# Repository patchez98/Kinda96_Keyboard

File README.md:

# Kinda96_Keyboard
Kinda a 96% keyboard, except the numpad is removable (and located on the left side) and there's a split spacebar. Also, it's wired/wireless thanks to the TinyPico Nano.

There are three KiCAD projects here, each with a different keyboard.

Full_96 holds a project with a single-board 96% keyboard. This is the simplest and cheapest option.

Full_75 holds a project with a 75% keyboard PCB. This board has a connector on the left side that can supply power to the numpad.

Numpad holds a project with a standalone wired/wireless numpad, with the option for power delivery from the 75% board.

I made the project like this for a number of reasons, the most notable being my ability to 3D print an entire case/plate in one go on my Artillery Sidewinder X1. Other than that, options are nice, I guess. Regardless, the full 96% board exists in case I get access to a larger printer sometime in the future.

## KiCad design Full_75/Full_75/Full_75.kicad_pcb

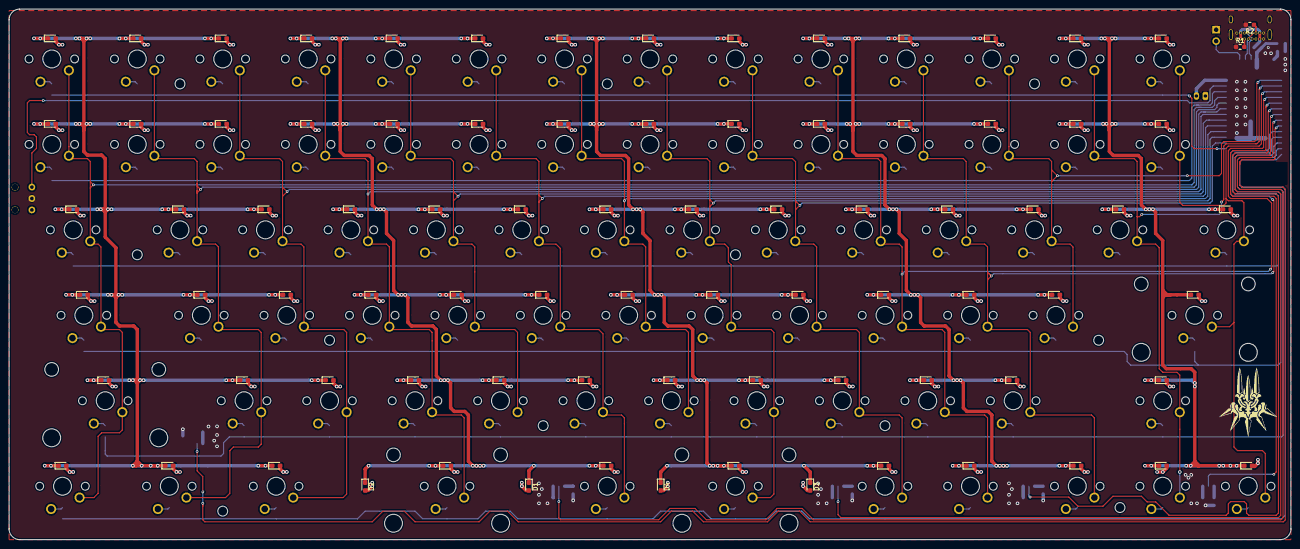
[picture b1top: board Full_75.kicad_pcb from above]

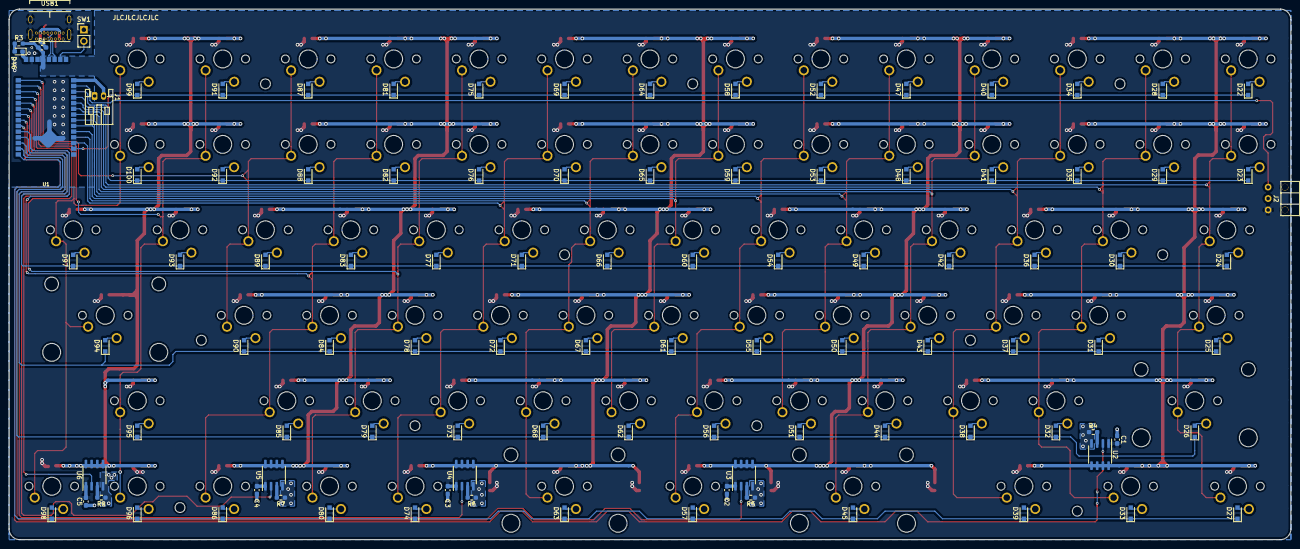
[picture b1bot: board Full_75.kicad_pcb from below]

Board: 2 copper layers, 285.7 x 118.3 mm, 185 parts (101 on the bottom side), 125 nets.

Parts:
C1, C2, C3, C4, C5: 2.2u; C_0603_1608Metric_Pad1.08x0.95mm_HandSolder
D1, D2, D3, D4: LED; LED_0603_1608Metric_Pad1.05x0.95mm_HandSolder
D22, D23, D24, D25, D26, D27, D28, D29, D30, D31, D32, D33, D34, D35, D36, D37, D38, D39, D40, D41, D42, D43, D44, D45, D47, D48, D49, D50, D51, D52, D53, D54, D55, D56, D57, D58, D59, D60, D61, D62, D63, D64, D65, D66, D67, D68, D69, D70, D71, D72, D73, D74, D75, D76, D77, D78, D79, D80, D81, D82, D83, D84, D85, D86, D87, D88, D89, D90, D91, D92, D93, D94, D95, D96, D97, D98, D99, D100: D; D_SOD-323_HandSoldering
D46: BATT_LED; LED_0603_1608Metric_Pad1.05x0.95mm_HandSolder
F1: 500mA; Fuse_0603_1608Metric_Pad1.05x0.95mm_HandSolder
J1: Battery; JST_PH_S2B-PH-K_1x02_P2.00mm_Horizontal
J2: Numpad_PWR; 01x03_MillMax_Springloaded_Pin
MX22: ESC; MXOnly-1U
MX23: `; MXOnly-1U
MX24: Tab; MXOnly-1.5U
MX25: Caps; MXOnly-1.75U
MX26: Shift; MXOnly-2.25U
MX27: LCtrl; MXOnly-1.25U
MX28: F1; MXOnly-1U
MX29: 1; MXOnly-1U
MX30: Q; MXOnly-1U
MX31: A; MXOnly-1U
MX32: Z; MXOnly-1U
MX33: Win; MXOnly-1.25U
MX34: F2; MXOnly-1U
MX35: 2; MXOnly-1U
MX36: W; MXOnly-1U
MX37: S; MXOnly-1U
MX38: X; MXOnly-1U
MX39: LAlt; MXOnly-1.25U
MX40: F3; MXOnly-1U
MX41: 3; MXOnly-1U
MX42: E; MXOnly-1U
MX43: D; MXOnly-1U
MX44: C; MXOnly-1U
MX45: Space; MXOnly-2.75U
MX46: F4; MXOnly-1U
MX47: 4; MXOnly-1U
MX48: R; MXOnly-1U
MX49: F; MXOnly-1U
MX50: V; MXOnly-1U
MX51: F5; MXOnly-1U
MX52: 5; MXOnly-1U
MX53: T; MXOnly-1U
MX54: G; MXOnly-1U
MX55: B; MXOnly-1U
MX56: Del; MXOnly-1U
MX57: F6; MXOnly-1U
MX58: 6; MXOnly-1U
MX59: Y; MXOnly-1U
MX60: H; MXOnly-1U
MX61: N; MXOnly-1U
MX62: Backspace; MXOnly-2U
MX63: F7; MXOnly-1U
MX64: 7; MXOnly-1U
MX65: U; MXOnly-1U
MX66: J; MXOnly-1U
MX67: M; MXOnly-1U
MX68: F8; MXOnly-1U
MX69: 8; MXOnly-1U
MX70: I; MXOnly-1U
MX71: K; MXOnly-1U
MX72: ,; MXOnly-1U
MX73: Home; MXOnly-1U
MX74: F9; MXOnly-1U
MX75: 9; MXOnly-1U
MX76: O; MXOnly-1U
MX77: L; MXOnly-1U
MX78: .; MXOnly-1U
MX79: End; MXOnly-1U
MX80: F10; MXOnly-1U
MX81: 0; MXOnly-1U
MX82: P; MXOnly-1U
MX83: ;; MXOnly-1U
MX84: /; MXOnly-1U
MX85: Left; MXOnly-1U
MX86: F11; MXOnly-1U
MX87: -; MXOnly-1U
MX88: [; MXOnly-1U
MX89: '; MXOnly-1U
MX90: F12; MXOnly-1U
MX91: =; MXOnly-1U
MX92: ]; MXOnly-1U
MX93: Enter; MXOnly-2.25U
MX94: Up; MXOnly-1U
MX95: Down; MXOnly-1U
MX96: \; MXOnly-1.5U
MX97: Right; MXOnly-1U
MX98: PgUp; MXOnly-1U
MX99: PgDn; MXOnly-1U
R1, R2: 5.1k; R_0603_1608Metric_Pad0.98x0.95mm_HandSolder
R3: 2k; R_0603_1608Metric_Pad0.98x0.95mm_HandSolder
R4, R5, R6, R7, R8: 16k; R_0603_1608Metric_Pad0.98x0.95mm_HandSolder
SW1: SW_DIP_x01; PinHeader_1x02_P2.54mm_Vertical
U1: TinyPICO_Nano
U2, U3, U4, U5, U6: MIC4801; SOIC-8_3.9x4.9mm_P1.27mm
USB1: USB4085-GF-A; USB_C_GCT_USB4085

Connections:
+5V: C1.2, C2.2, C3.2, C4.2, C5.2, D1.2, D2.2, D3.2, D4.2, F1.1, J2.1, MX22.3, MX23.3, MX24.3, MX25.3, MX26.3, MX27.3, MX28.3, MX29.3, MX30.3, MX31.3, MX32.3, MX33.3, MX34.3, MX35.3, MX36.3, MX37.3, MX38.3, MX39.3, MX40.3, MX41.3, MX42.3, MX43.3, MX44.3, MX45.3, MX46.3, MX47.3, MX48.3, MX49.3, MX50.3, MX51.3, MX52.3, MX53.3, MX54.3, MX55.3, MX56.3, MX57.3, MX58.3, MX59.3, MX60.3, MX61.3, MX62.3, MX63.3, MX64.3, MX65.3, MX66.3, MX67.3, MX68.3, MX69.3, MX70.3, MX71.3, MX72.3, MX73.3, MX74.3, MX75.3, MX76.3, MX77.3, MX78.3, MX79.3, MX80.3, MX81.3, MX82.3, MX83.3, MX84.3, MX85.3, MX86.3, MX87.3, MX88.3, MX89.3, MX90.3, MX91.3, MX92.3, MX93.3, MX94.3, MX95.3, MX96.3, MX97.3, MX98.3, MX99.3, R3.1, U1.4, U2.1, U3.1, U4.1, U5.1, U6.1
/Col[0]: MX22.1, MX23.1, MX24.1, MX25.1, MX26.1, MX27.1, U1.12
/Col[1]: MX28.1, MX29.1, MX30.1, MX31.1, MX32.1, MX33.1, U1.13
/Col[2]: MX34.1, MX35.1, MX36.1, MX37.1, MX38.1, MX39.1, U1.14
/Col[3]: MX40.1, MX41.1, MX42.1, MX43.1, MX44.1, MX45.1, U1.15
/Col[4]: MX46.1, MX47.1, MX48.1, MX49.1, MX50.1, U1.16
/Col[5]: MX51.1, MX52.1, MX53.1, MX54.1, MX55.1, MX56.1, U1.17
/Col[6]: MX57.1, MX58.1, MX59.1, MX60.1, MX61.1, U1.18
/Col[7]: MX62.1, MX63.1, MX64.1, MX65.1, MX66.1, MX67.1, U1.19
/Col[8]: MX68.1, MX69.1, MX70.1, MX71.1, MX72.1, MX73.1, U1.20
/Col[9]: MX74.1, MX75.1, MX76.1, MX77.1, MX78.1, MX79.1, U1.26
/Col[10]: MX80.1, MX81.1, MX82.1, MX83.1, MX84.1, MX85.1, U1.32
/Col[11]: MX86.1, MX87.1, MX88.1, MX89.1, U1.23
/Col[12]: MX90.1, MX91.1, MX92.1, MX94.1, MX95.1, U1.24
/Col[13]: MX93.1, MX96.1, MX97.1, MX98.1, MX99.1, U1.25
/LED_CAT0: MX22.4, MX23.4, MX24.4, MX25.4, MX26.4, MX27.4, MX28.4, MX29.4, MX30.4, MX31.4, MX32.4, MX33.4, MX34.4, MX35.4, MX36.4, MX37.4, MX38.4, MX39.4, U2.5, U2.6, U2.7, U2.8
/LED_CAT1: D1.1, D2.1, MX40.4, MX41.4, MX42.4, MX43.4, MX44.4, MX45.4, MX46.4, MX47.4, MX48.4, MX49.4, MX50.4, MX51.4, MX52.4, MX53.4, MX54.4, MX55.4, MX56.4, U3.5, U3.6, U3.7, U3.8
/LED_CAT2: D3.1, D4.1, MX57.4, MX58.4, MX59.4, MX60.4, MX61.4, MX62.4, MX63.4, MX64.4, MX65.4, MX66.4, MX67.4, MX68.4, MX69.4, MX70.4, MX71.4, MX72.4, MX73.4, U4.5, U4.6, U4.7, U4.8
/LED_CAT3: MX74.4, MX75.4, MX76.4, MX77.4, MX78.4, MX79.4, MX80.4, MX81.4, MX82.4, MX83.4, MX84.4, MX85.4, MX86.4, MX87.4, MX88.4, MX89.4, U5.5, U5.6, U5.7, U5.8
/LED_CAT4: MX90.4, MX91.4, MX92.4, MX93.4, MX94.4, MX95.4, MX96.4, MX97.4, MX98.4, MX99.4, U6.5, U6.6, U6.7, U6.8
/LED_EN0: U1.31, U2.2
/LED_EN1: U1.30, U3.2
/LED_EN2: U1.29, U4.2
/LED_EN3: U1.28, U5.2
/LED_EN4: U1.27, U6.2
/LED_EN_NUM: J2.3, U1.10
/Row[0]: D22.1, D28.1, D34.1, D40.1, D47.1, D52.1, D58.1, D64.1, D69.1, D75.1, D81.1, D87.1, D91.1, D99.1, U1.21
/Row[1]: D23.1, D29.1, D35.1, D41.1, D48.1, D53.1, D59.1, D65.1, D70.1, D76.1, D82.1, D88.1, D92.1, D100.1, U1.11
/Row[2]: D24.1, D30.1, D36.1, D42.1, D49.1, D54.1, D60.1, D66.1, D71.1, D77.1, D83.1, D89.1, D93.1, D97.1, U1.33
/Row[3]: D25.1, D31.1, D37.1, D43.1, D50.1, D55.1, D61.1, D67.1, D72.1, D78.1, D84.1, D90.1, D94.1, U1.34
/Row[4]: D26.1, D32.1, D38.1, D44.1, D51.1, D56.1, D62.1, D68.1, D73.1, D79.1, D85.1, D95.1, U1.35
/Row[5]: D27.1, D33.1, D39.1, D45.1, D57.1, D63.1, D74.1, D80.1, D86.1, D96.1, D98.1, U1.36
EN: SW1.2, U1.7
GND: C1.1, C2.1, C3.1, C4.1, C5.1, J1.1, J2.2, R1.1, R2.2, R4.1, R5.1, R6.1, R7.1, R8.1, SW1.1, U1.2, U2.4, U3.4, U4.4, U5.4, U6.4, USB1.A1, USB1.A12, USB1.B1, USB1.B12, USB1.S1
unnamed: D22.2, MX22.2
unnamed: D23.2, MX23.2
unnamed: D24.2, MX24.2
unnamed: D25.2, MX25.2
unnamed: D26.2, MX26.2
unnamed: D27.2, MX27.2
unnamed: D28.2, MX28.2
unnamed: D29.2, MX29.2
unnamed: D30.2, MX30.2
unnamed: D31.2, MX31.2
unnamed: D32.2, MX32.2
unnamed: D33.2, MX33.2
unnamed: D34.2, MX34.2
unnamed: D35.2, MX35.2
unnamed: D36.2, MX36.2
unnamed: D37.2, MX37.2
unnamed: D38.2, MX38.2
unnamed: D39.2, MX39.2
unnamed: D40.2, MX40.2
unnamed: D41.2, MX41.2
unnamed: D42.2, MX42.2
unnamed: D43.2, MX43.2
unnamed: D44.2, MX44.2
unnamed: D45.2, MX45.2
unnamed: D46.1, U1.1
unnamed: D46.2, R3.2
unnamed: D47.2, MX46.2
unnamed: D48.2, MX47.2
unnamed: D49.2, MX48.2
unnamed: D50.2, MX49.2
unnamed: D51.2, MX50.2
unnamed: D52.2, MX51.2
unnamed: D53.2, MX52.2
unnamed: D54.2, MX53.2
unnamed: D55.2, MX54.2
unnamed: D56.2, MX55.2
unnamed: D57.2, MX56.2
unnamed: D58.2, MX57.2
unnamed: D59.2, MX58.2
unnamed: D60.2, MX59.2
unnamed: D61.2, MX60.2
unnamed: D62.2, MX61.2
unnamed: D63.2, MX62.2
unnamed: D64.2, MX63.2
unnamed: D65.2, MX64.2
unnamed: D66.2, MX65.2
unnamed: D67.2, MX66.2
unnamed: D68.2, MX67.2
unnamed: D69.2, MX68.2
unnamed: D70.2, MX69.2
unnamed: D71.2, MX70.2
unnamed: D72.2, MX71.2
unnamed: D73.2, MX72.2
unnamed: D74.2, MX73.2
unnamed: D75.2, MX74.2
unnamed: D76.2, MX75.2
unnamed: D77.2, MX76.2
unnamed: D78.2, MX77.2
unnamed: D79.2, MX78.2
unnamed: D80.2, MX79.2
unnamed: D81.2, MX80.2
unnamed: D82.2, MX81.2
unnamed: D83.2, MX82.2
unnamed: D84.2, MX83.2
unnamed: D85.2, MX84.2
unnamed: D86.2, MX85.2
unnamed: D87.2, MX86.2
unnamed: D88.2, MX87.2
unnamed: D89.2, MX88.2
unnamed: D90.2, MX89.2
unnamed: D91.2, MX90.2
unnamed: D92.2, MX91.2
unnamed: D93.2, MX92.2
unnamed: D94.2, MX93.2
unnamed: D95.2, MX94.2
unnamed: D96.2, MX95.2
unnamed: D97.2, MX96.2
unnamed: D98.2, MX97.2
unnamed: D99.2, MX98.2
unnamed: D100.2, MX99.2
unnamed: F1.2, USB1.A4, USB1.A9, USB1.B4, USB1.B9
unnamed: J1.2, U1.9
unnamed: R1.2, USB1.A5
unnamed: R2.1, USB1.B5
unnamed: R4.2, U2.3
unnamed: R5.2, U3.3
unnamed: R6.2, U4.3
unnamed: R7.2, U5.3
unnamed: R8.2, U6.3
USB_D+: U1.6, USB1.A6, USB1.B6
USB_D-: U1.5, USB1.A7, USB1.B7

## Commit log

2021-06-17 Initial commit, pretty much done
2021-07-18 Libraries moved to global location, layout started for Full_75
2021-07-30 finished 75% layout
2021-10-01 LED code functional, working on switch matrix and profile storage
